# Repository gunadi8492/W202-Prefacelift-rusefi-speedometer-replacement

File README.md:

# Mercedes-Benz W202 Speedometer Replacement (rusEFI)

This project is a custom **speedometer replacement** for a **1994 Mercedes-Benz W202 C180 (pre-facelift)** running on a **rusEFI open-source standalone ECU**.  

⚠️ **Disclaimer:**  
This is an **open-source project** provided *as-is*, without any warranty or support.  
It is intended strictly for **educational and hobbyist purposes only**.  

---

## 📖 Background

This project builds upon the excellent work by [Pazi88](https://github.com/pazi88/E12_CAN_gauges), originally designed for a BMW E12 speedometer.  

Test implementation has been successfully tested with **rusEFI Dash CANBUS** with a BMW E46 CAN Dash setting, supporting:  
- **RPM**  
- **VSS (Vehicle Speed Sensor)**  
- **CLT (Coolant Temperature)**  

---

## 📟 Hardware Integration

For this adaptation, additional components were introduced:  
- **Nextion Enhanced 3.5” display**  
- **STM32F103C8T6 “Blue Pill” MCU**  

These allow enhanced visualization of live ECU data.  

The **schematic and hardware design** were adapted specifically to meet the requirements of this W202 project.  

---

## 💻 Firmware Status

- Development for the **STM32F103C8T6** firmware is still in progress.  
- For working code examples and inspiration, refer to Pazi’s original repository.  

---

## ⚠️ Important Notice

- ✅ **Responsibility**: You are solely responsible for checking and complying with all **local laws and regulations** before using this project.  
- ✅ **Road Use**: Compliance with vehicle safety and legal standards for public road use is mandatory.  
- ✅ **Liability**: No liability is accepted for misuse, damages, or legal issues resulting from use of this project.  
- 🚫 **Commercial Use**: Strictly prohibited.  
- 📌 **Recommendation**: Ensure you fully understand the project before attempting implementation.  

---

## 📜 License

This project is open-source, non-commercial, and intended for **educational/hobbyist purposes only**.  
Please respect the open-source spirit of this project — it is not to be used for making money

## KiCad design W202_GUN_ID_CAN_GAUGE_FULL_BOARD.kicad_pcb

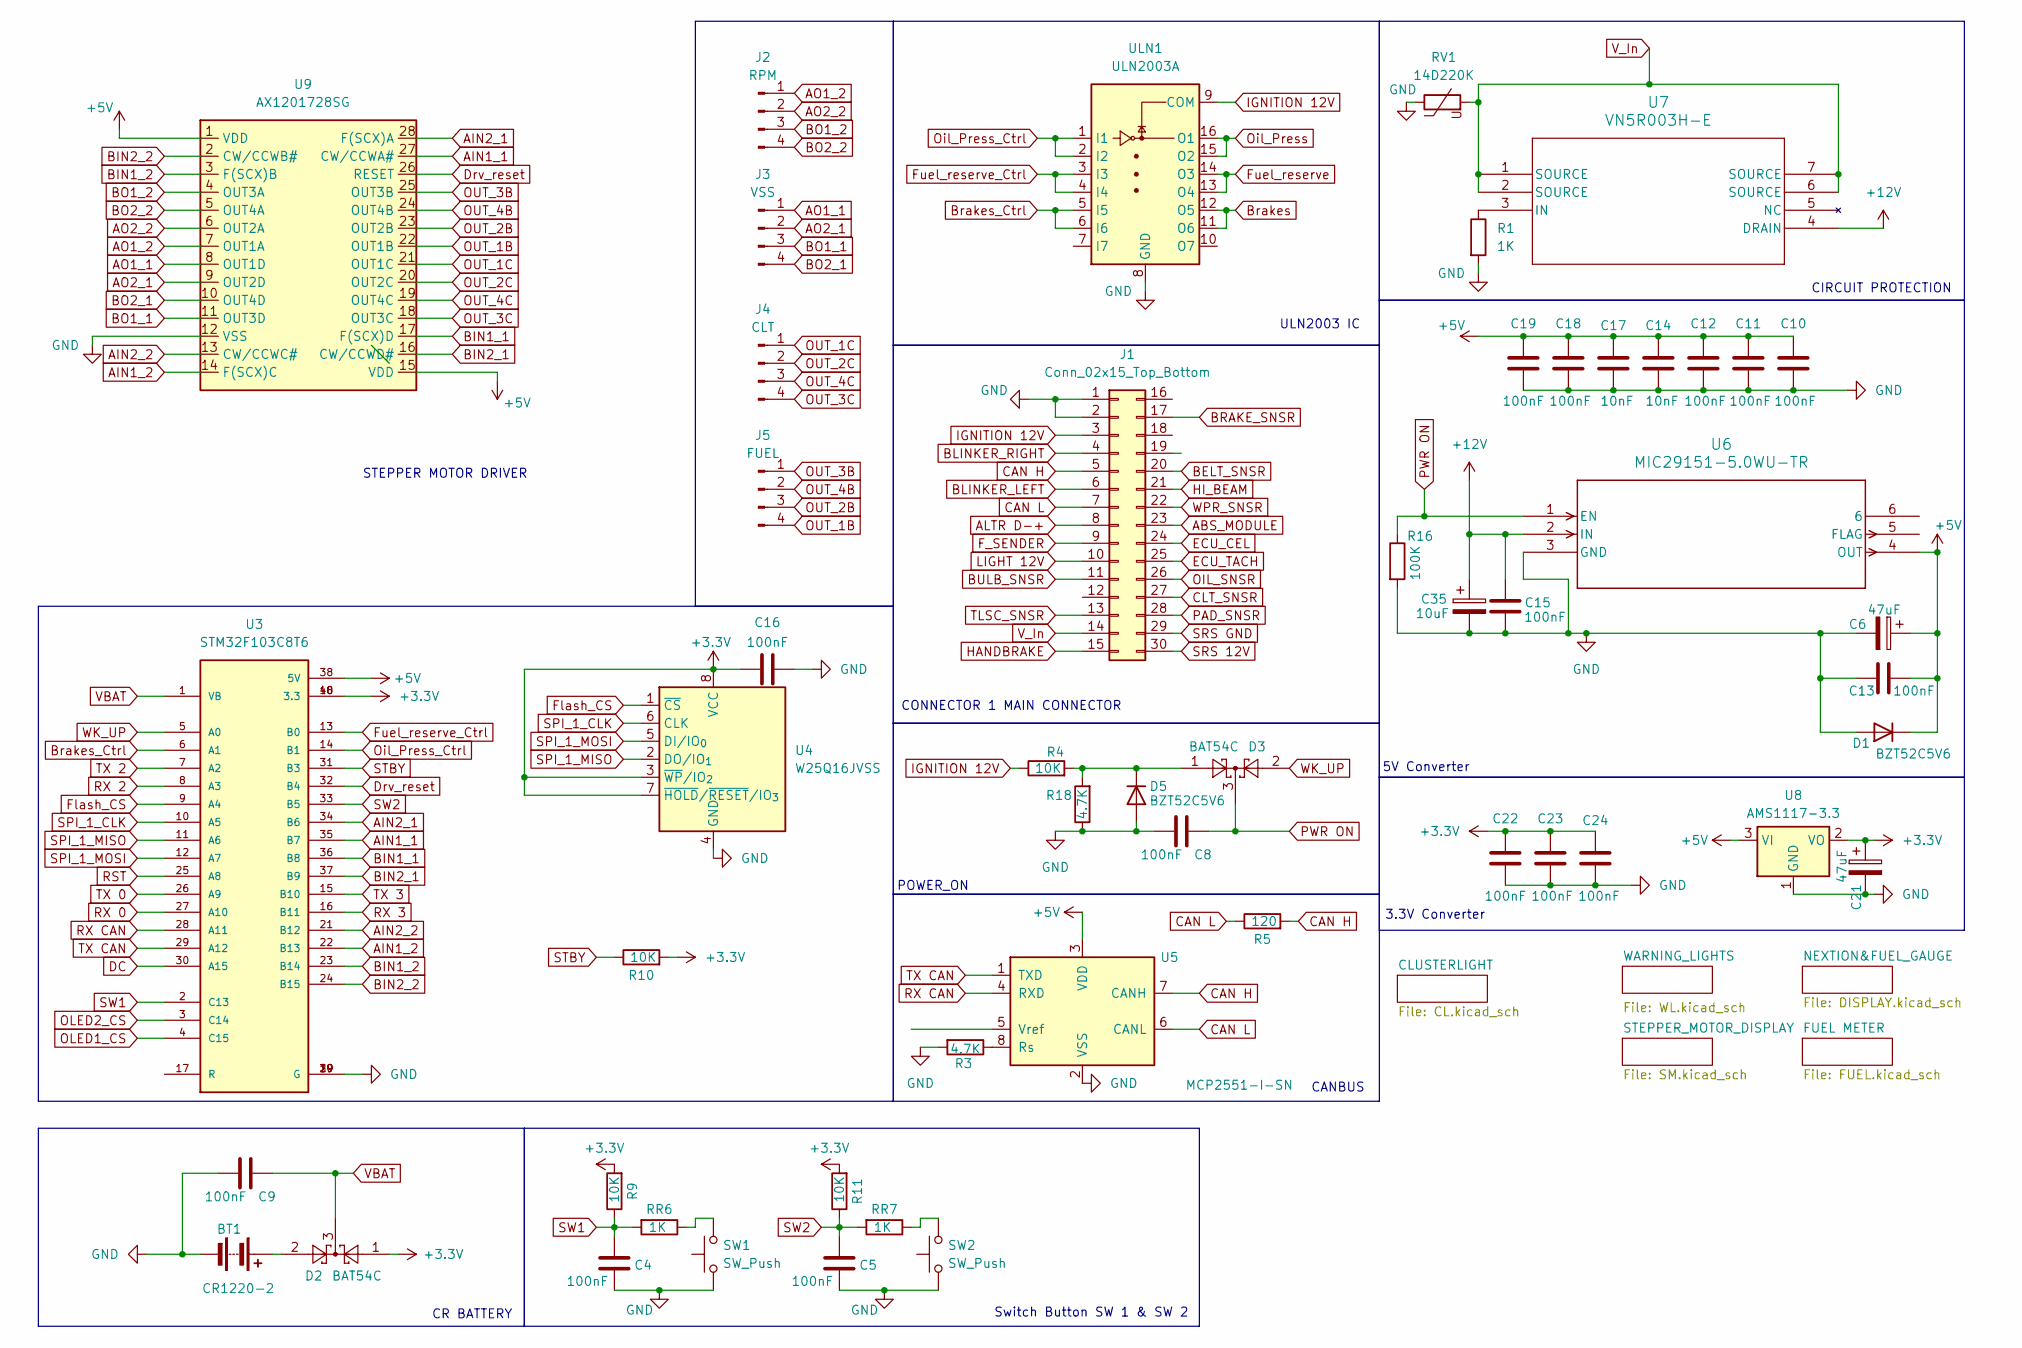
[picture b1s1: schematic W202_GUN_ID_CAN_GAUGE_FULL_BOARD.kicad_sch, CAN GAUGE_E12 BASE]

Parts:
BT1: CR1220-2; HARWIN_S8411-45R
C4, C5, C8, C9, C10, C11, C12, C13, C15, C16, C18, C19, C22, C23, C24: 100nF; C_0805_2012Metric
C6, C21: 47uF; CP_EIA-3528-21_Kemet-B_HandSolder
C14, C17: 10nF; C_0805_2012Metric
C35: 10uF; CP_EIA-3216-18_Kemet-A_HandSolder
D1, D5: BZT52C5V6; D_SOD-123
D2, D3: BAT54C; SOT-23
J1: Conn_02x15_Top_Bottom; IDC-Header_2x15_P2.54mm_Vertical
J2: RPM; PinHeader_1x04_P2.54mm_Vertical
J3: VSS; PinHeader_1x04_P2.54mm_Vertical
J4: CLT; PinHeader_1x04_P2.54mm_Vertical
J5: FUEL; PinHeader_1x04_P2.54mm_Vertical
R1: 1K; R_0805_2012Metric
R3, R18: 4.7K; R_0805_2012Metric
R4, R9, R10, R11: 10K; R_0805_2012Metric
R5: 120; R_0805_2012Metric
R16: 100K; R_0805_2012Metric
RR6, RR7: 1K; R_0805_2012Metric
RV1: 14D220K; RV_Disc_D12mm_W4.2mm_P7.5mm
SW1, SW2: SW_Push; SW_PUSH_6mm
U3: STM32F103C8T6; MODULE_ZC323000; PARTREV N/A
U4: W25Q16JVSS; SOIC-8_5.3x5.3mm_P1.27mm
U5: MCP2551-I-SN; SOIC-8_3.9x4.9mm_P1.27mm
U6: MIC29151-5.0WU-TR; TO-263-5_MCH
U7: VN5R003H-E; HPAK_R003H-E_STM
U8: AMS1117-3.3; SOT-223-3_TabPin2
U9: AX1201728SG; SOIC-28W_7.5x17.9mm_P1.27mm
ULN1: ULN2003A; SOIC-16_3.9x9.9mm_P1.27mm

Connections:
+3.3V: C16.2, C21.1, C22.1, C23.1, C24.1, D2.1, R9.2, R10.2, R11.2, U3.18 (3.3), U3.40 (3.3), U4.3 (~WP/IO_{2}), U4.7 (~HOLD/~RESET/IO_{3}), U4.8 (VCC), U8.2 (VO); also elsewhere on the board
+5V: C6.1, C10.1, C11.1, C12.1, C13.1, C14.1, C17.1, C18.1, C19.1, D1.1 (K), U3.38 (5V), U5.3 (VDD), U6.4 (OUT), U8.3 (VI), U9.1 (VDD), U9.15 (VDD); also elsewhere on the board
+12V: C15.1, C35.1, U6.2 (IN), U7.4 (DRAIN)
ABS_MODULE: J1.23; also elsewhere on the board
AIN1_1: U3.35 (B7), U9.27 (CW/CCWA#)
AIN1_2: U3.22 (B13), U9.14 (F(SCX)C)
AIN2_1: U3.34 (B6), U9.28 (F(SCX)A)
AIN2_2: U3.21 (B12), U9.13 (CW/CCWC#)
ALTR D-+: J1.8; also elsewhere on the board
AO1_1: J3.1, U9.8 (OUT1D); also elsewhere on the board
AO1_2: J2.1, U9.7 (OUT1A); also elsewhere on the board
AO2_1: J3.2, U9.9 (OUT2D); also elsewhere on the board
AO2_2: J2.2, U9.6 (OUT2A); also elsewhere on the board
BELT_SNSR: J1.20; also elsewhere on the board
BIN1_1: U3.36 (B8), U9.17 (F(SCX)D)
BIN1_2: U3.23 (B14), U9.3 (F(SCX)B)
BIN2_1: U3.37 (B9), U9.16 (CW/CCWD#)
BIN2_2: U3.24 (B15), U9.2 (CW/CCWB#)
BLINKER_LEFT: J1.6; also elsewhere on the board
BLINKER_RIGHT: J1.4; also elsewhere on the board
BO1_1: J3.3, U9.11 (OUT3D); also elsewhere on the board
BO1_2: J2.3, U9.4 (OUT3A); also elsewhere on the board
BO2_1: J3.4, U9.10 (OUT4D); also elsewhere on the board
BO2_2: J2.4, U9.5 (OUT4A); also elsewhere on the board
BRAKE_SNSR: J1.15, J1.17; also elsewhere on the board
BULB_SNSR: J1.11; also elsewhere on the board
Brakes_Ctrl: U3.6 (A1), ULN1.5 (I5), ULN1.6 (I6)
CAN H: J1.5, R5.2, U5.7 (CANH); also elsewhere on the board
CAN L: J1.7, R5.1, U5.6 (CANL); also elsewhere on the board
CLT_SNSR: J1.27; also elsewhere on the board
DC: U3.30 (A15); also elsewhere on the board
Drv_reset: U3.32 (B4), U9.26 (RESET)
ECU_CEL: J1.24; also elsewhere on the board
ECU_TACH: J1.25; also elsewhere on the board
F_SENDER: J1.9; also elsewhere on the board
Flash_CS: U3.9 (A4), U4.1 (~CS)
Fuel_reserve_Ctrl: U3.13 (B0), ULN1.3 (I3), ULN1.4 (I4)
GND: BT1.2 (-), C4.2, C5.2, C6.2, C8.2, C9.2, C10.2, C11.2, C12.2, C13.2, C14.2, C15.2, C16.1, C17.2, C18.2, C19.2, C21.2, C22.2, C23.2, C24.2, C35.2, D1.2 (A), D5.2 (A), J1.1, J1.2, R1.2, R3.2, R16.2, R18.1, RV1.1, SW1.1, SW2.1, U3.19 (G), U3.20 (G), U3.39 (G), U4.4 (GND), U5.2 (VSS), U6.3 (GND), U8.1 (GND), U9.12 (VSS), ULN1.8 (GND); also elsewhere on the board
HI_BEAM: J1.21; also elsewhere on the board
LIGHT 12V: J1.10; also elsewhere on the board
unnamed: BT1.1 (+), D2.2
unnamed: D3.1, D5.1 (K), R4.2, R18.2
unnamed: RR6.1, SW1.2
unnamed: RR7.1, SW2.2
unnamed: R3.1, U5.8 (Rs)
unnamed: R1.1, U7.3 (IN)
unnamed: ULN1.11 (O6), ULN1.12 (O5)
unnamed: ULN1.13 (O4), ULN1.14 (O3)
unnamed: ULN1.15 (O2), ULN1.16 (O1)
OIL_SNSR: J1.26; also elsewhere on the board
OLED1_CS: U3.4 (C15); also elsewhere on the board
OLED2_CS: U3.3 (C14); also elsewhere on the board
OUT_1B: J5.4, U9.22 (OUT1B)
OUT_1C: J4.1, U9.21 (OUT1C); also elsewhere on the board
OUT_2B: J5.3, U9.23 (OUT2B)
OUT_2C: J4.2, U9.20 (OUT2C); also elsewhere on the board
OUT_3B: J5.1, U9.25 (OUT3B)
OUT_3C: J4.4, U9.18 (OUT3C); also elsewhere on the board
OUT_4B: J5.2, U9.24 (OUT4B)
OUT_4C: J4.3, U9.19 (OUT4C); also elsewhere on the board
Oil_Press_Ctrl: U3.14 (B1), ULN1.1 (I1), ULN1.2 (I2)
PAD_SNSR: J1.28; also elsewhere on the board
PWR ON: C8.1, D3.3, R16.1, U6.1 (EN)
RST: U3.25 (A8); also elsewhere on the board
RX 0: U3.27 (A10)
RX 2: U3.8 (A3)
RX 3: U3.16 (B11)
RX CAN: U3.28 (A11), U5.4 (RXD); also elsewhere on the board
SPI_1_CLK: U3.10 (A5), U4.6 (CLK); also elsewhere on the board
SPI_1_MISO: U3.11 (A6), U4.2 (DO/IO_{1})
SPI_1_MOSI: U3.12 (A7), U4.5 (DI/IO_{0}); also elsewhere on the board
SRS 12V: J1.30; also elsewhere on the board
SRS GND: J1.29; also elsewhere on the board
STBY: R10.1, U3.31 (B3)
SW1: C4.1, R9.1, RR6.2, U3.2 (C13)
SW2: C5.1, R11.1, RR7.2, U3.33 (B5)
TLSC_SNSR: J1.13; also elsewhere on the board
TX 0: U3.26 (A9)
TX 2: U3.7 (A2)
TX 3: U3.15 (B10)
TX CAN: U3.29 (A12), U5.1 (TXD); also elsewhere on the board
VBAT: C9.1, D2.3, U3.1 (VB)
V_In: J1.14, RV1.2, U7.1 (SOURCE), U7.2 (SOURCE), U7.6 (SOURCE), U7.7 (SOURCE)
WK_UP: D3.2, U3.5 (A0)
WPR_SNSR: J1.22; also elsewhere on the board

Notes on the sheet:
ULN2003 IC
CONNECTOR 1 MAIN CONNECTOR
POWER_ON
CR BATTERY
3.3V Converter
CANBUS
CIRCUIT PROTECTION
Switch Button SW 1 & SW 2
STEPPER MOTOR DRIVER
5V Converter

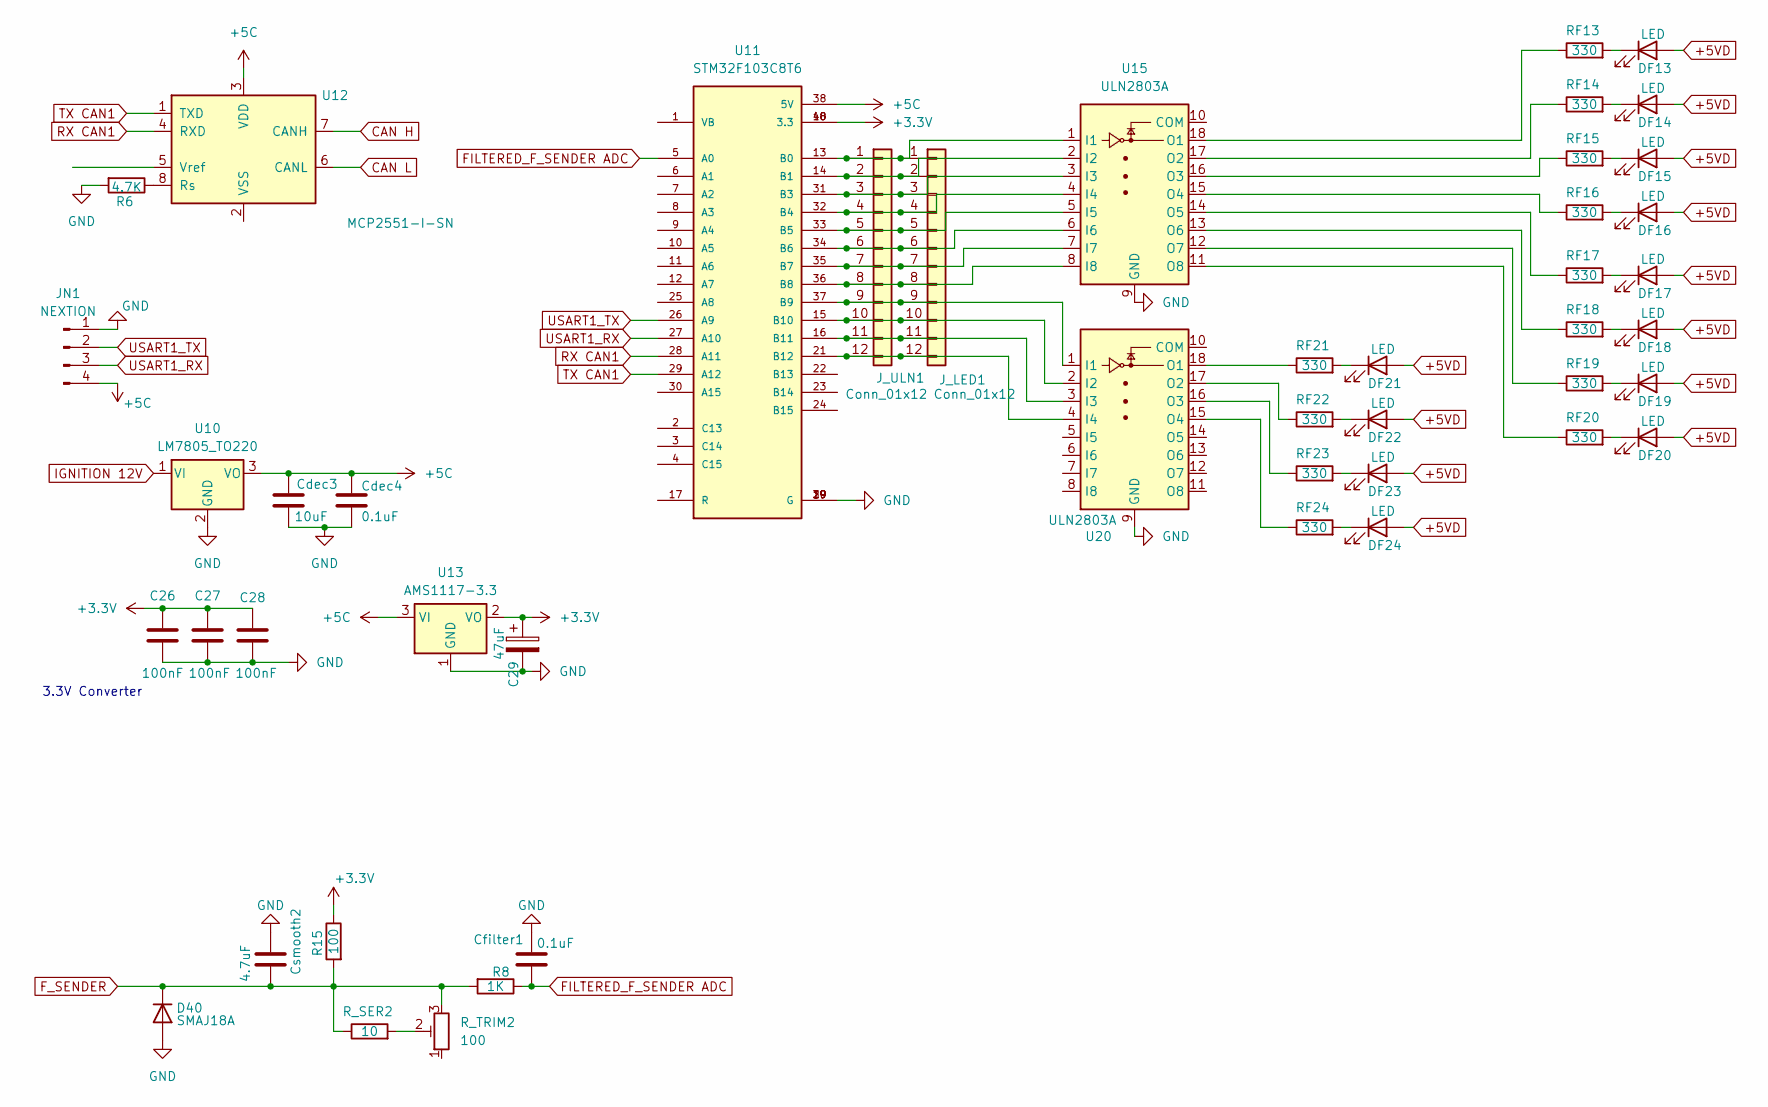
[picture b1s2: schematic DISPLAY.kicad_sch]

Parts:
C26, C27, C28: 100nF; C_0805_2012Metric
C29: 47uF; CP_EIA-3528-21_Kemet-B_HandSolder
Cdec3: 10uF; C_0805_2012Metric
Cdec4: 0.1uF; C_0805_2012Metric
Cfilter1: 0.1uF; C_0805_2012Metric
Csmooth2: 4.7uF; C_0805_2012Metric
D40: SMAJ18A; D_SMA
DF13, DF14, DF15, DF16, DF17, DF18, DF19, DF20, DF21, DF22, DF23, DF24: LED; LED_0805_2012Metric
JN1: NEXTION; PinHeader_1x04_P2.54mm_Vertical
J_LED1: Conn_01x12; PinHeader_1x12_P2.00mm_Horizontal
J_ULN1: Conn_01x12; PinHeader_1x12_P2.00mm_Horizontal
R6: 4.7K; R_0805_2012Metric
R8: 1K; R_0805_2012Metric
R15: 100; R_2512_6332Metric
RF13, RF14, RF15, RF16, RF17, RF18, RF19, RF20, RF21, RF22, RF23, RF24: 330; R_0603_1608Metric
R_SER2: 10; R_2512_6332Metric
R_TRIM2: 100; Potentiometer_Bourns_3314J_Vertical
U10: LM7805_TO220; TO-220-3_Vertical
U11: STM32F103C8T6; MODULE_ZC323000; PARTREV N/A
U12: MCP2551-I-SN; SOIC-8_3.9x4.9mm_P1.27mm
U13: AMS1117-3.3; SOT-223-3_TabPin2
U15, U20: ULN2803A; SOIC-20W_7.5x12.8mm_P1.27mm

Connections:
+3.3V: C26.1, C27.1, C28.1, C29.1, R15.1, U11.18 (3.3), U11.40 (3.3), U13.2 (VO); also elsewhere on the board
+5C: Cdec3.1, Cdec4.1, JN1.4, U10.3 (VO), U11.38 (5V), U12.3 (VDD), U13.3 (VI); also elsewhere on the board
+5VD: DF13.2 (A), DF14.2 (A), DF15.2 (A), DF16.2 (A), DF17.2 (A), DF18.2 (A), DF19.2 (A), DF20.2 (A), DF21.2 (A), DF22.2 (A), DF23.2 (A), DF24.2 (A); also elsewhere on the board
CAN H: U12.7 (CANH); also elsewhere on the board
CAN L: U12.6 (CANL); also elsewhere on the board
FILTERED_F_SENDER ADC: Cfilter1.1, R8.1, U11.5 (A0)
F_SENDER: Csmooth2.2, D40.1 (K), R8.2, R15.2, R_SER2.1, R_TRIM2.3; also elsewhere on the board
GND: C26.2, C27.2, C28.2, C29.2, Cdec3.2, Cdec4.2, Cfilter1.2, Csmooth2.1, D40.2 (A), JN1.1, R6.2, U10.2 (GND), U11.19 (G), U11.20 (G), U11.39 (G), U13.1 (GND), U15.9 (GND), U20.9 (GND); also elsewhere on the board
unnamed: DF13.1 (K), RF13.2
unnamed: DF14.1 (K), RF14.2
unnamed: DF15.1 (K), RF15.2
unnamed: DF16.1 (K), RF16.2
unnamed: DF17.1 (K), RF17.2
unnamed: DF18.1 (K), RF18.2
unnamed: DF19.1 (K), RF19.2
unnamed: DF20.1 (K), RF20.2
unnamed: DF21.1 (K), RF21.2
unnamed: DF22.1 (K), RF22.2
unnamed: DF23.1 (K), RF23.2
unnamed: DF24.1 (K), RF24.2
unnamed: J_LED1.1, J_ULN1.1, U11.13 (B0), U15.1 (I1)
unnamed: J_LED1.2, J_ULN1.2, U11.14 (B1), U15.2 (I2)
unnamed: J_LED1.3, J_ULN1.3, U11.31 (B3), U15.3 (I3)
unnamed: J_LED1.4, J_ULN1.4, U11.32 (B4), U15.4 (I4)
unnamed: J_LED1.5, J_ULN1.5, U11.33 (B5), U15.5 (I5)
unnamed: J_LED1.6, J_ULN1.6, U11.34 (B6), U15.6 (I6)
unnamed: J_LED1.7, J_ULN1.7, U11.35 (B7), U15.7 (I7)
unnamed: J_LED1.8, J_ULN1.8, U11.36 (B8), U15.8 (I8)
unnamed: J_LED1.9, J_ULN1.9, U11.37 (B9), U20.1 (I1)
unnamed: J_LED1.10, J_ULN1.10, U11.15 (B10), U20.2 (I2)
unnamed: J_LED1.11, J_ULN1.11, U11.16 (B11), U20.3 (I3)
unnamed: J_LED1.12, J_ULN1.12, U11.21 (B12), U20.4 (I4)
unnamed: R_SER2.2, R_TRIM2.2
unnamed: R6.1, U12.8 (Rs)
unnamed: RF13.1, U15.18 (O1)
unnamed: RF14.1, U15.17 (O2)
unnamed: RF15.1, U15.16 (O3)
unnamed: RF16.1, U15.15 (O4)
unnamed: RF17.1, U15.14 (O5)
unnamed: RF18.1, U15.13 (O6)
unnamed: RF19.1, U15.12 (O7)
unnamed: RF20.1, U15.11 (O8)
unnamed: RF21.1, U20.18 (O1)
unnamed: RF22.1, U20.17 (O2)
unnamed: RF23.1, U20.16 (O3)
unnamed: RF24.1, U20.15 (O4)
RX CAN1: U11.28 (A11), U12.4 (RXD)
TX CAN1: U11.29 (A12), U12.1 (TXD)
USART1_RX: JN1.3, U11.27 (A10)
USART1_TX: JN1.2, U11.26 (A9)

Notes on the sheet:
3.3V Converter

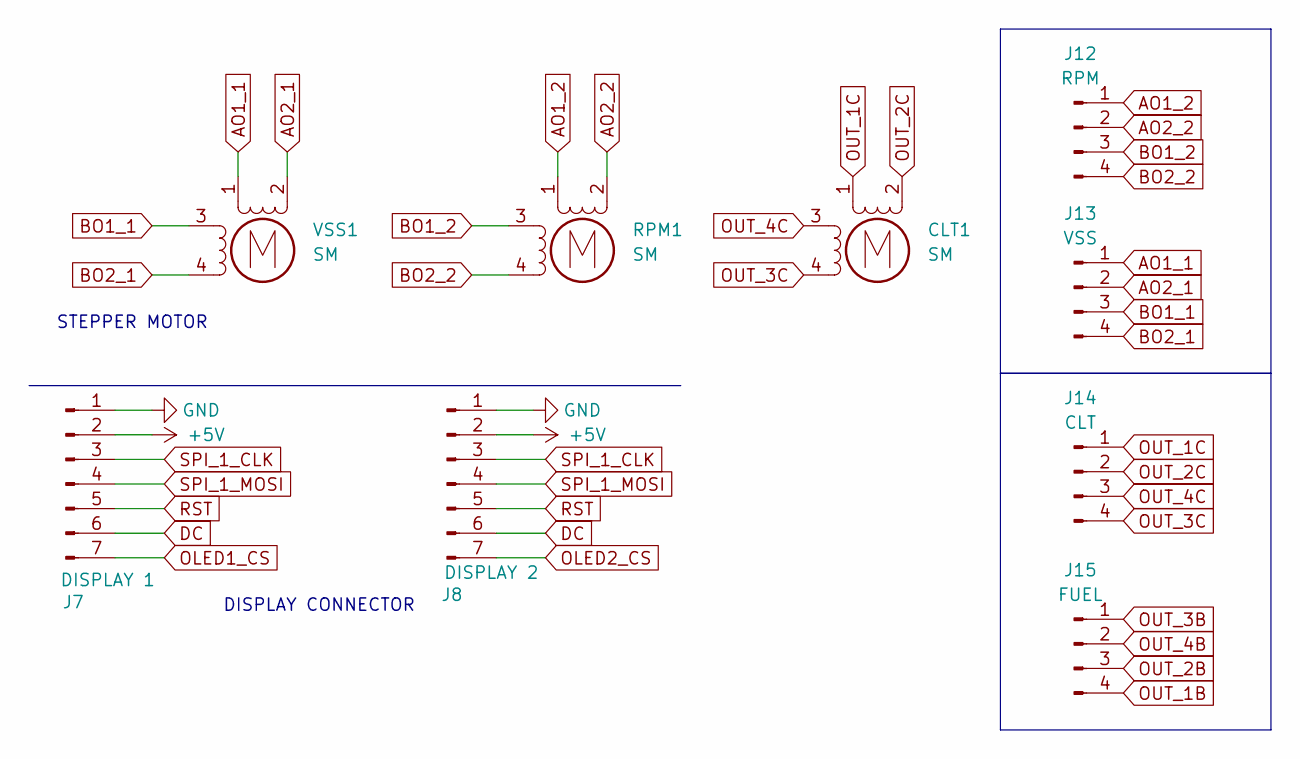
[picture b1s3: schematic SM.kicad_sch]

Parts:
CLT1: SM; X27-168__V2
J7: DISPLAY 1; PinHeader_1x07_P2.54mm_Vertical
J8: DISPLAY 2; PinHeader_1x07_P2.54mm_Vertical
J12: RPM; PinHeader_1x04_P2.54mm_Vertical
J13: VSS; PinHeader_1x04_P2.54mm_Vertical
J14: CLT; PinHeader_1x04_P2.54mm_Vertical
J15: FUEL; PinHeader_1x04_P2.54mm_Vertical
RPM1: SM; X27-168__V2
VSS1: SM; X27-168__V2

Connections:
+5V: J7.2, J8.2; also elsewhere on the board
AO1_1: J13.1, VSS1.1; also elsewhere on the board
AO1_2: J12.1, RPM1.1; also elsewhere on the board
AO2_1: J13.2, VSS1.2 (-); also elsewhere on the board
AO2_2: J12.2, RPM1.2 (-); also elsewhere on the board
BO1_1: J13.3, VSS1.3; also elsewhere on the board
BO1_2: J12.3, RPM1.3; also elsewhere on the board
BO2_1: J13.4, VSS1.4; also elsewhere on the board
BO2_2: J12.4, RPM1.4; also elsewhere on the board
DC: J7.6, J8.6; also elsewhere on the board
GND: J7.1, J8.1; also elsewhere on the board
OLED1_CS: J7.7; also elsewhere on the board
OLED2_CS: J8.7; also elsewhere on the board
OUT_1C: CLT1.1, J14.1; also elsewhere on the board
OUT_2C: CLT1.2 (-), J14.2; also elsewhere on the board
OUT_3C: CLT1.4, J14.4; also elsewhere on the board
OUT_4C: CLT1.3, J14.3; also elsewhere on the board
RST: J7.5, J8.5; also elsewhere on the board
SPI_1_CLK: J7.3, J8.3; also elsewhere on the board
SPI_1_MOSI: J7.4, J8.4; also elsewhere on the board

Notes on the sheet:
DISPLAY CONNECTOR
STEPPER MOTOR

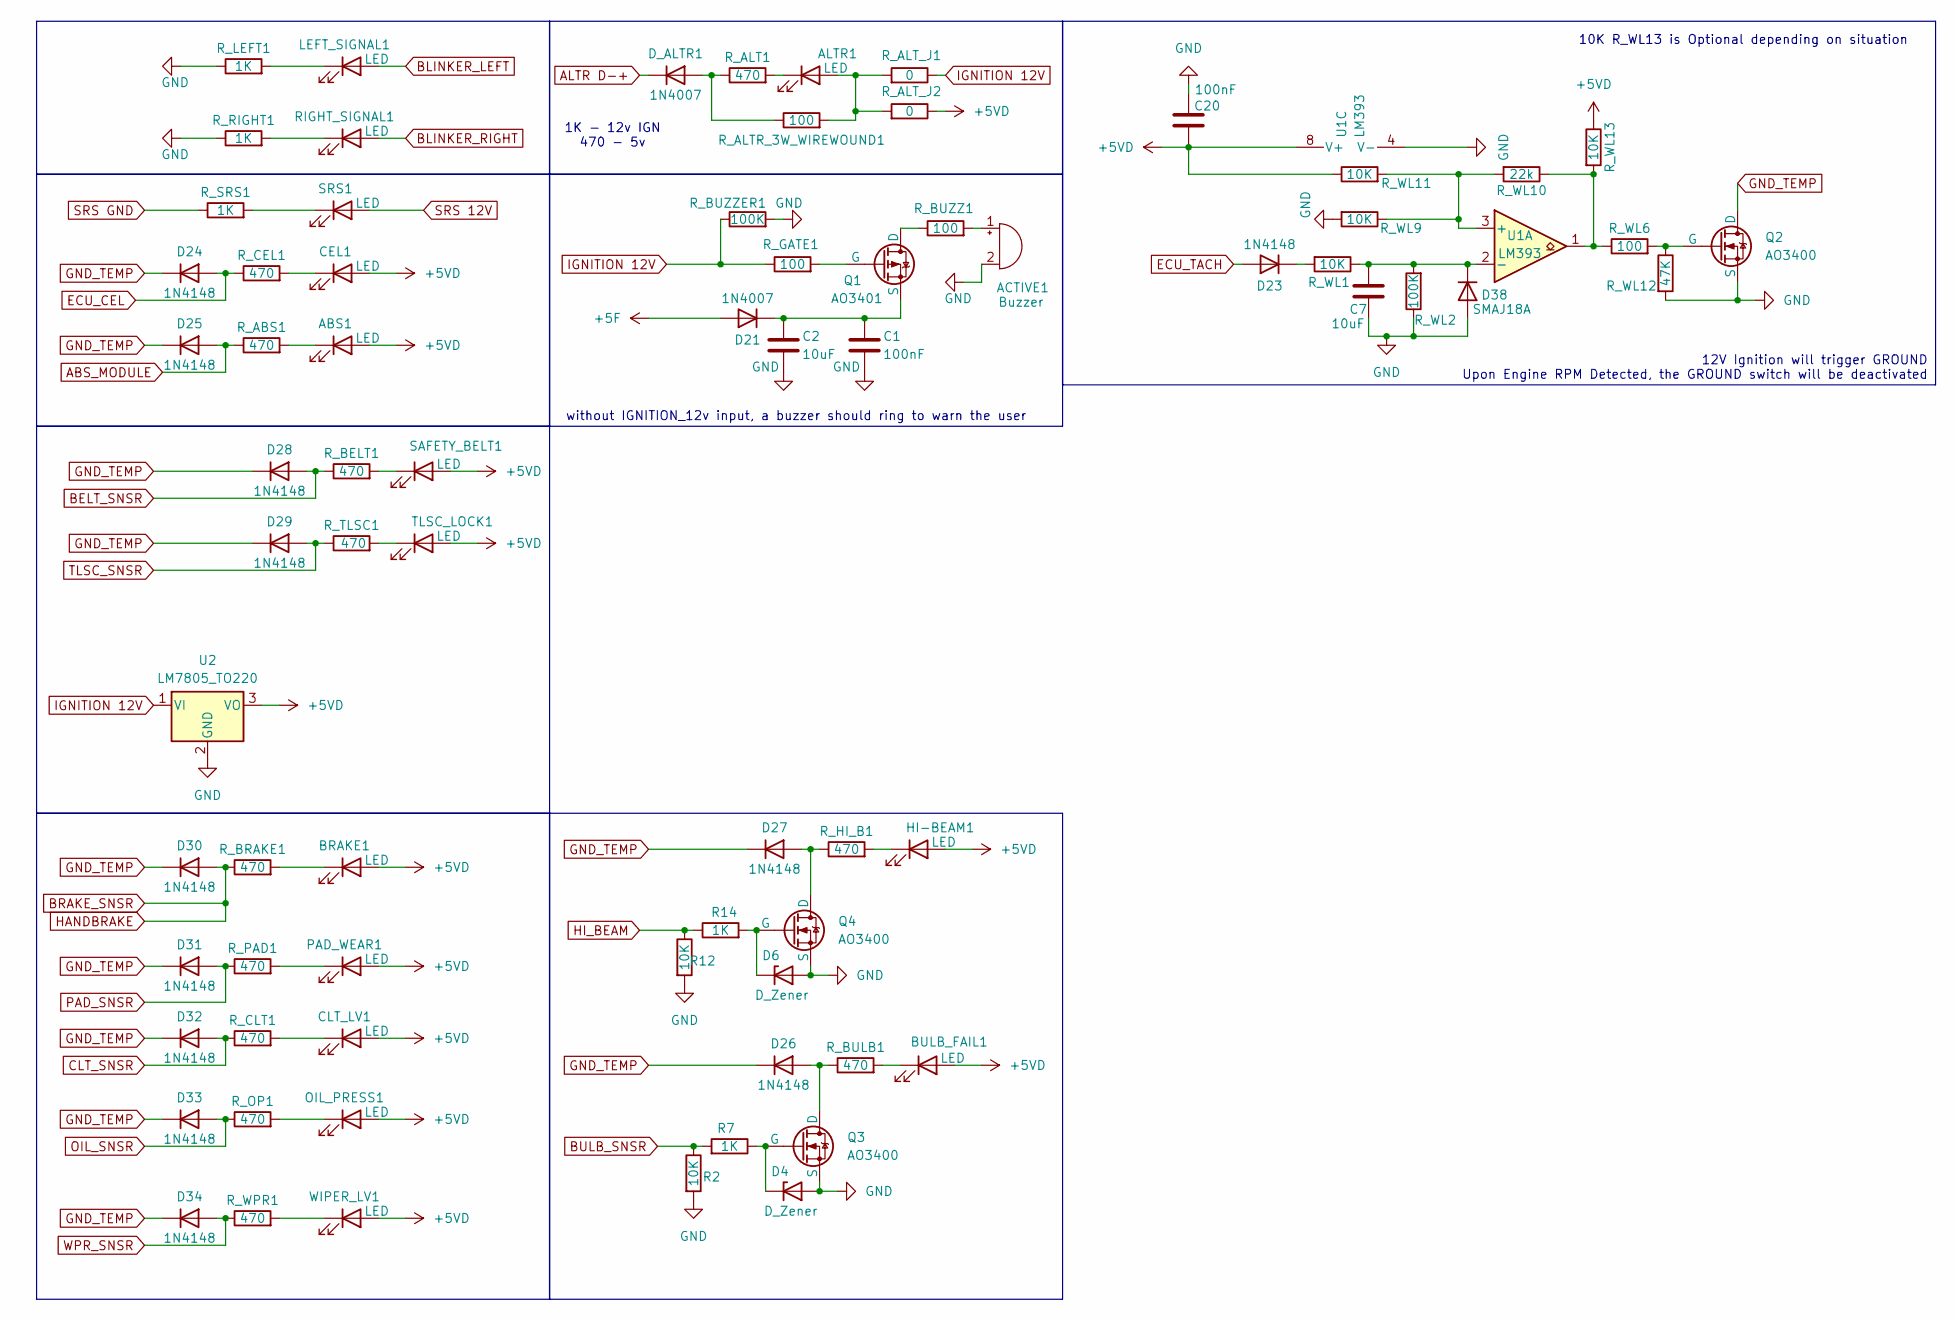
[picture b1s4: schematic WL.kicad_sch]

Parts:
ABS1: LED; LED_Everlight-SMD3528_3.5x2.8mm_67-21ST
ACTIVE1: Buzzer; Buzzer_TDK_PS1240P02BT_D12.2mm_H6.5mm
ALTR1: LED; LED_Everlight-SMD3528_3.5x2.8mm_67-21ST
BRAKE1: LED; LED_Everlight-SMD3528_3.5x2.8mm_67-21ST
BULB_FAIL1: LED; LED_Everlight-SMD3528_3.5x2.8mm_67-21ST
C1, C20: 100nF; C_0805_2012Metric
C2, C7: 10uF; C_0805_2012Metric
CEL1: LED; LED_Everlight-SMD3528_3.5x2.8mm_67-21ST
CLT_LV1: LED; LED_Everlight-SMD3528_3.5x2.8mm_67-21ST
D4, D6: D_Zener; D_MiniMELF
D21: 1N4007; D_SMA_Handsoldering
D23, D24, D25, D26, D27, D28, D29, D30, D31, D32, D33, D34: 1N4148; D_SOD-123
D38: SMAJ18A; D_SMA
D_ALTR1: 1N4007; D_SMA_Handsoldering
HI-BEAM1: LED; LED_Everlight-SMD3528_3.5x2.8mm_67-21ST
LEFT_SIGNAL1: LED; LED_Everlight-SMD3528_3.5x2.8mm_67-21ST
OIL_PRESS1: LED; LED_Everlight-SMD3528_3.5x2.8mm_67-21ST
PAD_WEAR1: LED; LED_Everlight-SMD3528_3.5x2.8mm_67-21ST
Q1: AO3401; SOT-23
Q2, Q3, Q4: AO3400; SOT-23
R2, R12: 10K; R_0805_2012Metric
R7, R14: 1K; R_0805_2012Metric
RIGHT_SIGNAL1: LED; LED_Everlight-SMD3528_3.5x2.8mm_67-21ST
R_ABS1: 470; R_0805_2012Metric
R_ALT1: 470; R_0805_2012Metric
R_ALTR_3W_WIREWOUND1: 100; Fuse_Littelfuse-NANO2-462
R_ALT_J1, R_ALT_J2: 0; R_0805_2012Metric
R_BELT1: 470; R_0805_2012Metric
R_BRAKE1: 470; R_0805_2012Metric
R_BULB1: 470; R_0805_2012Metric
R_BUZZ1: 100; R_0805_2012Metric
R_BUZZER1: 100K; R_0805_2012Metric
R_CEL1: 470; R_0805_2012Metric
R_CLT1: 470; R_0805_2012Metric
R_GATE1: 100; R_0805_2012Metric
R_HI_B1: 470; R_0805_2012Metric
R_LEFT1: 1K; R_1210_3225Metric_Pad1.30x2.65mm_HandSolder
R_OP1: 470; R_0805_2012Metric
R_PAD1: 470; R_0805_2012Metric
R_RIGHT1: 1K; R_1210_3225Metric_Pad1.30x2.65mm_HandSolder
R_SRS1: 1K; R_1206_3216Metric
R_TLSC1: 470; R_0805_2012Metric
R_WL1, R_WL9, R_WL11, R_WL13: 10K; R_0805_2012Metric
R_WL2: 100K; R_0805_2012Metric
R_WL6: 100; R_0805_2012Metric
R_WL10: 22k; R_0805_2012Metric
R_WL12: 47K; R_0805_2012Metric
R_WPR1: 470; R_0805_2012Metric
SAFETY_BELT1: LED; LED_Everlight-SMD3528_3.5x2.8mm_67-21ST
SRS1: LED; LED_Everlight-SMD3528_3.5x2.8mm_67-21ST
TLSC_LOCK1: LED; LED_Everlight-SMD3528_3.5x2.8mm_67-21ST
U1: LM393; SO08
U2: LM7805_TO220; TO-220-3_Vertical
WIPER_LV1: LED; LED_Everlight-SMD3528_3.5x2.8mm_67-21ST

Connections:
+5F: D21.2 (A); also elsewhere on the board
+5VD: ABS1.2 (A), BRAKE1.2 (A), BULB_FAIL1.2 (A), C20.1, CEL1.2 (A), CLT_LV1.2 (A), HI-BEAM1.2 (A), OIL_PRESS1.2 (A), PAD_WEAR1.2 (A), R_ALT_J2.1, R_WL11.1, R_WL13.1, SAFETY_BELT1.2 (A), TLSC_LOCK1.2 (A), U1.8 (V+), U2.3 (VO), WIPER_LV1.2 (A); also elsewhere on the board
ABS_MODULE: D25.2 (A), R_ABS1.1; also elsewhere on the board
ALTR D-+: D_ALTR1.1 (K); also elsewhere on the board
BELT_SNSR: D28.2 (A), R_BELT1.1; also elsewhere on the board
BLINKER_LEFT: LEFT_SIGNAL1.2 (A); also elsewhere on the board
BLINKER_RIGHT: RIGHT_SIGNAL1.2 (A); also elsewhere on the board
BRAKE_SNSR: D30.2 (A), R_BRAKE1.1; also elsewhere on the board
BULB_SNSR: R2.1, R7.2; also elsewhere on the board
CLT_SNSR: D32.2 (A), R_CLT1.1; also elsewhere on the board
ECU_CEL: D24.2 (A), R_CEL1.1; also elsewhere on the board
ECU_TACH: D23.2 (A); also elsewhere on the board
GND: ACTIVE1.2 (-), C1.2, C2.2, C7.2, C20.2, D4.2 (A), D6.2 (A), D38.2 (A), Q2.3 (S), Q3.3 (S), Q4.3 (S), R2.2, R12.2, R_BUZZER1.2, R_LEFT1.1, R_RIGHT1.1, R_WL2.1, R_WL9.2, R_WL12.2, U1.4 (V-), U2.2 (GND); also elsewhere on the board
GND_TEMP: D24.1 (K), D25.1 (K), D26.1 (K), D27.1 (K), D28.1 (K), D29.1 (K), D30.1 (K), D31.1 (K), D32.1 (K), D33.1 (K), D34.1 (K), Q2.1 (D)
HI_BEAM: R12.1, R14.1; also elsewhere on the board
unnamed: ABS1.1 (K), R_ABS1.2
unnamed: ACTIVE1.1 (+), R_BUZZ1.2
unnamed: ALTR1.2 (A), R_ALTR_3W_WIREWOUND1.2, R_ALT_J1.2, R_ALT_J2.2
unnamed: ALTR1.1 (K), R_ALT1.2
unnamed: BRAKE1.1 (K), R_BRAKE1.2
unnamed: BULB_FAIL1.1 (K), R_BULB1.2
unnamed: CEL1.1 (K), R_CEL1.2
unnamed: CLT_LV1.1 (K), R_CLT1.2
unnamed: D4.1 (K), Q3.2 (G), R7.1
unnamed: D6.1 (K), Q4.2 (G), R14.2
unnamed: C1.1, C2.1, D21.1 (K), Q1.3 (S)
unnamed: D23.1 (K), R_WL1.2
unnamed 69: D26.2 (A), Q3.1 (D), R_BULB1.1; also elsewhere on the board
unnamed 70: D27.2 (A), Q4.1 (D), R_HI_B1.1; also elsewhere on the board
unnamed: C7.1, D38.1 (K), R_WL1.1, R_WL2.2, U1.2 (-)
unnamed: D_ALTR1.2 (A), R_ALT1.1, R_ALTR_3W_WIREWOUND1.1
unnamed: HI-BEAM1.1 (K), R_HI_B1.2
unnamed: LEFT_SIGNAL1.1 (K), R_LEFT1.2
unnamed: OIL_PRESS1.1 (K), R_OP1.2
unnamed: PAD_WEAR1.1 (K), R_PAD1.2
unnamed: Q1.1 (D), R_BUZZ1.1
unnamed: Q1.2 (G), R_GATE1.2
unnamed 104: Q2.2 (G), R_WL6.2, R_WL12.1; also elsewhere on the board
unnamed: RIGHT_SIGNAL1.1 (K), R_RIGHT1.2
unnamed: R_WL6.1, R_WL10.1, R_WL13.2, U1.1
unnamed: R_BELT1.2, SAFETY_BELT1.1 (K)
unnamed: R_SRS1.2, SRS1.1 (K)
unnamed: R_TLSC1.2, TLSC_LOCK1.1 (K)
unnamed: R_WL9.1, R_WL10.2, R_WL11.2, U1.3 (+)
unnamed: R_WPR1.2, WIPER_LV1.1 (K)
OIL_SNSR: D33.2 (A), R_OP1.1; also elsewhere on the board
PAD_SNSR: D31.2 (A), R_PAD1.1; also elsewhere on the board
SRS 12V: SRS1.2 (A); also elsewhere on the board
SRS GND: R_SRS1.1; also elsewhere on the board
TLSC_SNSR: D29.2 (A), R_TLSC1.1; also elsewhere on the board
WPR_SNSR: D34.2 (A), R_WPR1.1; also elsewhere on the board

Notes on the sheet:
1K - 12v IGN 470 - 5v
10K R_WL13 is Optional depending on situation
without IGNITION_12v input, a buzzer should ring to warn the user
12V Ignition will trigger GROUND Upon Engine RPM Detected, the GROUND switch will be deactivated

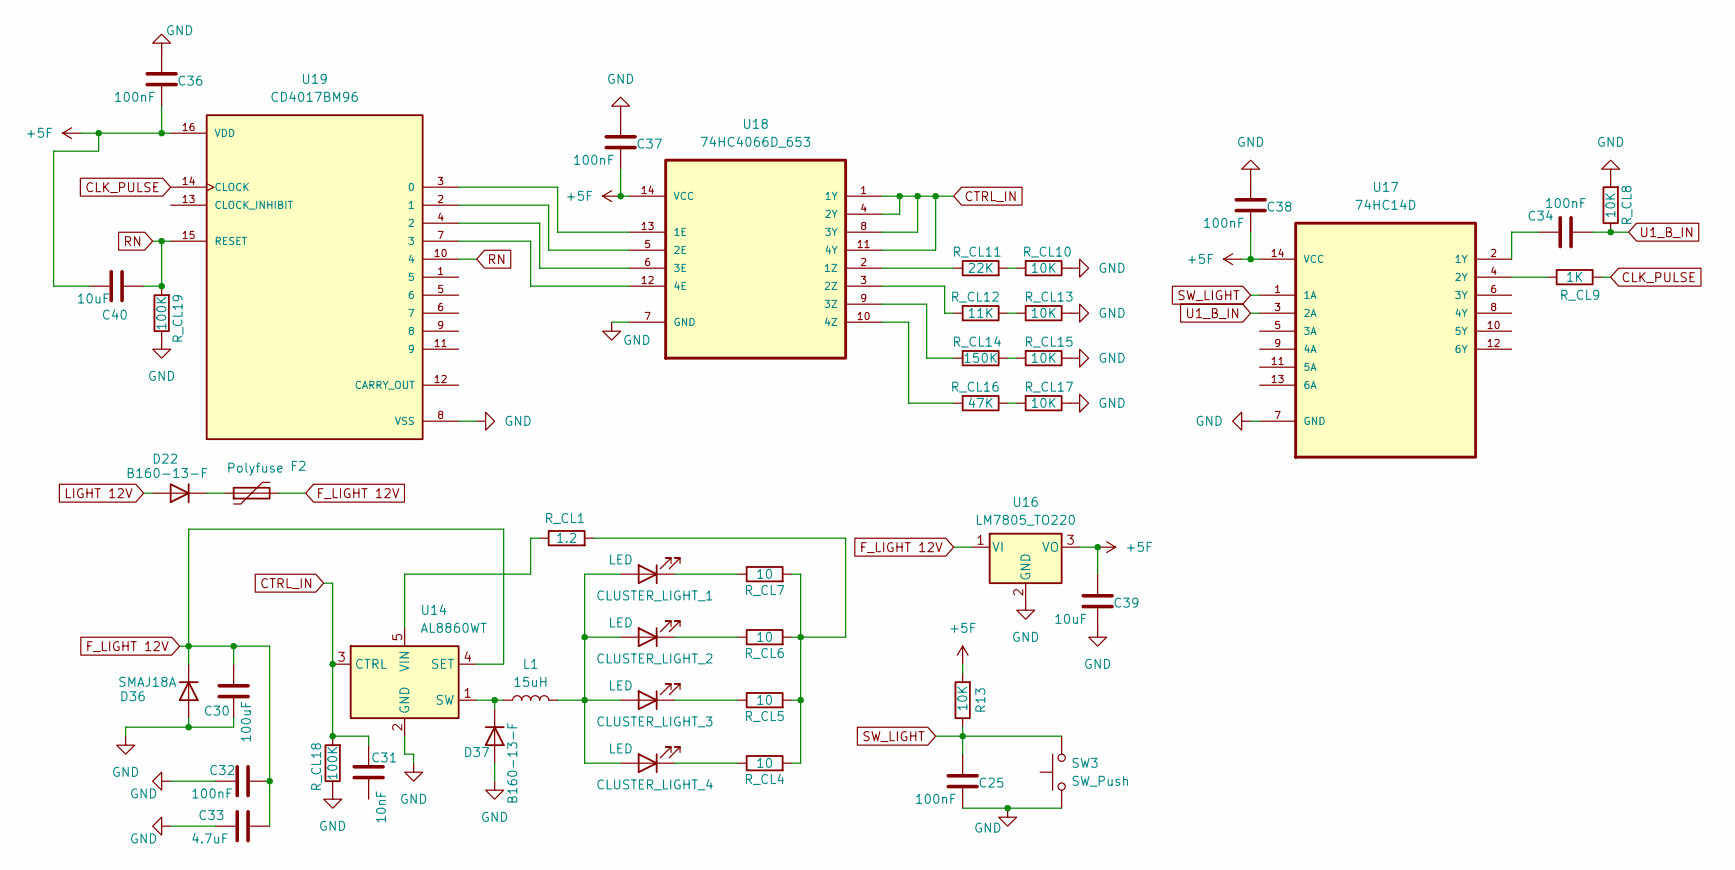
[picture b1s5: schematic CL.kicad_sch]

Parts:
C25, C32, C34, C36, C37, C38: 100nF; C_0805_2012Metric
C30: 100uF; CP_EIA-7343-31_Kemet-D_HandSolder
C31: 10nF; C_0805_2012Metric
C33: 4.7uF; C_0805_2012Metric
C39, C40: 10uF; C_0805_2012Metric
CLUSTER_LIGHT_1, CLUSTER_LIGHT_2, CLUSTER_LIGHT_3, CLUSTER_LIGHT_4: LED; LED_Everlight-SMD3528_3.5x2.8mm_67-21ST
D22: B160-13-F; D_SMA_Handsoldering
D36: SMAJ18A; D_SMA
D37: B160-13-F; D_SMA
F2: Polyfuse; Fuse_1206_3216Metric_Pad1.42x1.75mm_HandSolder
L1: 15uH; L_Vishay_IFSC-1515AH_4x4x1.8mm
R13: 10K; R_0805_2012Metric
R_CL1: 1.2; R_2512_6332Metric
R_CL4, R_CL5, R_CL6, R_CL7: 10; R_0805_2012Metric
R_CL8, R_CL10, R_CL13, R_CL15, R_CL17: 10K; R_0805_2012Metric
R_CL9: 1K; R_0805_2012Metric
R_CL11: 22K; R_0805_2012Metric
R_CL12: 11K; R_0805_2012Metric
R_CL14: 150K; R_0805_2012Metric
R_CL16: 47K; R_0805_2012Metric
R_CL18, R_CL19: 100K; R_0805_2012Metric
SW3: SW_Push; SW_PUSH_6mm
U14: AL8860WT; TSOT-23-5
U16: LM7805_TO220; TO-220-3_Vertical
U17: 74HC14D; SOIC127P600X175-14N; MPN 74HC14D
U18: 74HC4066D_653; SOIC127P600X175-14N; MPN 74HC4066D,653
U19: CD4017BM96; SOIC127P600X175-16N; PARTREV Feb 2004

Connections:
+5F: C36.2, C37.2, C38.2, C39.1, C40.2, R13.2, U16.3 (VO), U17.14 (VCC), U18.14 (VCC), U19.16 (VDD); also elsewhere on the board
CLK_PULSE: R_CL9.1, U19.14 (CLOCK)
CTRL_IN: C31.1, R_CL18.2, U14.3 (CTRL), U18.1 (1Y), U18.4 (2Y), U18.8 (3Y), U18.11 (4Y)
F_LIGHT 12V: C30.1, C32.1, C33.1, D36.1 (K), F2.2, U14.4 (SET), U16.1 (VI)
GND: C25.2, C30.2, C32.2, C33.2, C36.1, C37.1, C38.1, C39.2, D36.2 (A), D37.2 (A), R_CL8.2, R_CL10.1, R_CL13.1, R_CL15.1, R_CL17.1, R_CL18.1, R_CL19.1, SW3.1, U14.2 (GND), U16.2 (GND), U17.7 (GND), U18.7 (GND), U19.8 (VSS); also elsewhere on the board
LIGHT 12V: D22.2 (A); also elsewhere on the board
unnamed: CLUSTER_LIGHT_1.2 (A), CLUSTER_LIGHT_2.2 (A), CLUSTER_LIGHT_3.2 (A), CLUSTER_LIGHT_4.2 (A), L1.2
unnamed: CLUSTER_LIGHT_1.1 (K), R_CL7.1
unnamed: CLUSTER_LIGHT_2.1 (K), R_CL6.1
unnamed: CLUSTER_LIGHT_3.1 (K), R_CL5.1
unnamed: CLUSTER_LIGHT_4.1 (K), R_CL4.1
unnamed: D22.1 (K), F2.1
unnamed: D37.1 (K), L1.1, U14.1 (SW)
unnamed: R_CL1.2, R_CL4.2, R_CL5.2, R_CL6.2, R_CL7.2
unnamed: R_CL10.2, R_CL11.2
unnamed: R_CL12.1, R_CL13.2
unnamed: R_CL14.1, R_CL15.2
unnamed: R_CL16.1, R_CL17.2
unnamed: R_CL1.1, U14.5 (VIN)
unnamed: C34.1, U17.2 (1Y)
unnamed: R_CL9.2, U17.4 (2Y)
unnamed: U18.13 (1E), U19.3 (0)
unnamed: R_CL11.1, U18.2 (1Z)
unnamed: U18.5 (2E), U19.2 (1)
unnamed: R_CL12.2, U18.3 (2Z)
unnamed: U18.6 (3E), U19.4 (2)
unnamed: R_CL14.2, U18.9 (3Z)
unnamed: U18.12 (4E), U19.7 (3)
unnamed: R_CL16.2, U18.10 (4Z)
RN: C40.1, R_CL19.2, U19.10 (4), U19.15 (RESET)
SW_LIGHT: C25.1, R13.1, SW3.2, U17.1 (1A)
U1_B_IN: C34.2, R_CL8.1, U17.3 (2A)

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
